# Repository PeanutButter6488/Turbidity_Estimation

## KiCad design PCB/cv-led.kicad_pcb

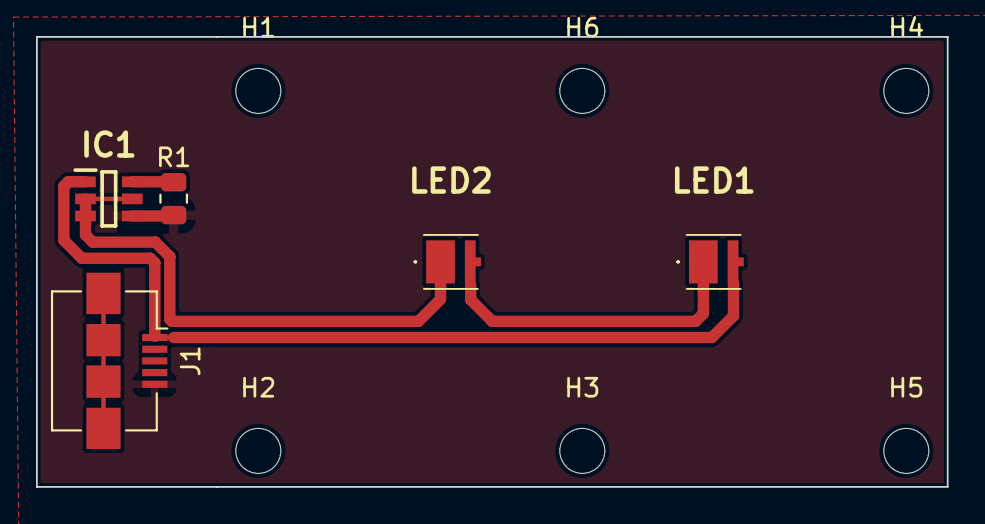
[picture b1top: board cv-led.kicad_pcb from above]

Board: 2 copper layers, 50.6 x 25.0 mm, 11 parts (0 on the bottom side), 5 nets.

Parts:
H1, H2, H3, H4, H5, H6: MountingHole; MountingHole_2.5mm
IC1: BCR420UW6Q-7; SOT95P285X140-6N
J1: USB3_B_Micro; USB_Micro-B_Amphenol_10104110_Horizontal
LED1, LED2: JB3030AWT-P-H65EA0000-N0000001; JB3030AWTPH65EA0000N0000001
R1: R_US; R_0805_2012Metric

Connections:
/out: IC1.2 (OUT_1), IC1.3 (OUT_2), IC1.5 (OUT_3), LED2.1
GND: IC1.4 (GND), J1.5 (GND), R1.2
unnamed: IC1.6 (REXT), R1.1
unnamed: LED1.1, LED2.2
VCC: IC1.1 (EN), J1.1 (VBUS), LED1.2

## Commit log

2022-08-17 Update codes
2022-08-17 Update figures
2022-08-17 added holder design
2022-08-17 added cuvette holder
2022-08-17 added pcb
2022-08-17 added
2022-08-17 Add comments
2022-08-19 Generate model and test fit pdfs
2022-08-20 Update field test images
2022-08-22 added more image asses
2022-08-23 Update code
2022-08-23 Update images
2022-08-24 Update test sample only
2022-08-24 working
2022-08-25 Add pdf
2022-08-27 Update process model
2022-08-27 Update project
2022-08-27 git ignore
